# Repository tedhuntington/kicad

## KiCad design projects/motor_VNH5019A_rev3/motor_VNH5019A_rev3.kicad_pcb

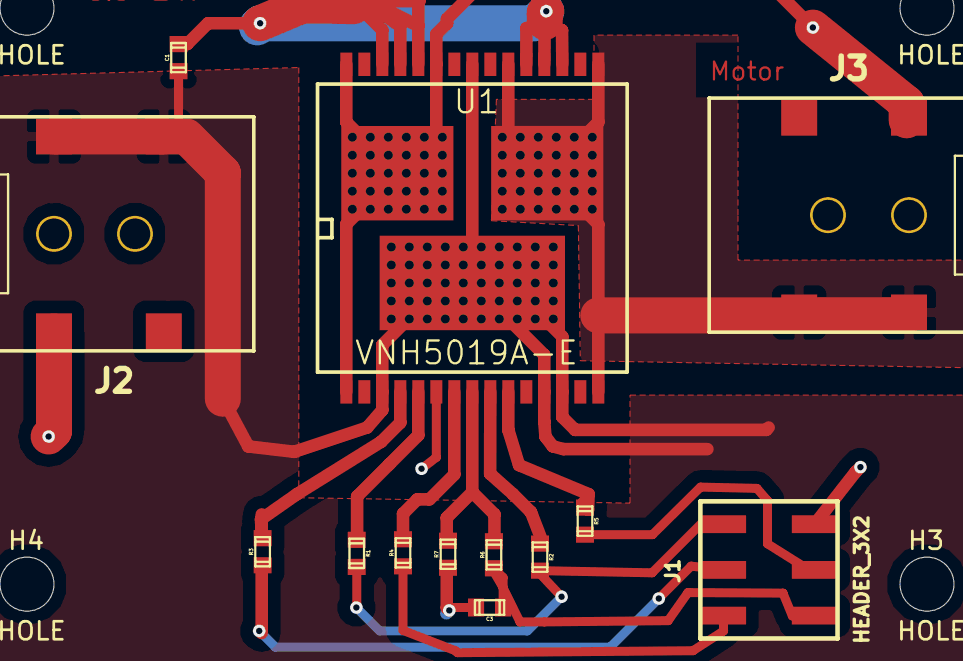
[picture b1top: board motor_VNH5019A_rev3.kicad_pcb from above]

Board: 2 copper layers, 17 parts (0 on the bottom side), 15 nets.

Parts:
C1: .1uF (50v); TED_SM0603
C3: 33nF; TED_SM0603
H1, H2, H3, H4: HOLE; TED_Hole_3mm
J1: HEADER_3X2; TED_HEADER_3x2_SMT
J2, J3: DC_2.1MM; TED_DC_2.1mm_SMT
R1, R2: 3.3k; TED_SM0603
R3, R4, R5: 1k; TED_SM0603
R6: 10k; TED_SM0603
R7: 1.5k; TED_SM0603
U1: VNH5019A-E; TED_MultiPowerSO-30

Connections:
+2.8v: J1.1, R1.2, R2.2
CS: R6.2, R7.2, U1.8
GND: C1.2, C3.2, J1.6, J2.2, R7.1, U1.6, U1.18, U1.19, U1.20, U1.26, U1.27, U1.28
IN_A: R3.2, U1.4
IN_B: R5.1, U1.10
Motor1OutA: J3.2, U1.1, U1.25, U1.30, U1.33
Motor1OutB: J3.1, U1.15, U1.16, U1.21, U1.32
unnamed: J1.3, R4.1
unnamed: R2.1, U1.9
unnamed: R1.1, U1.5
unnamed: J1.2, R3.1
unnamed: J1.5, R5.2
unnamed: C3.1, J1.4, R6.1
PWM: R4.2, U1.7
Vin: C1.1, J2.1, U1.3, U1.12, U1.13, U1.23, U1.31

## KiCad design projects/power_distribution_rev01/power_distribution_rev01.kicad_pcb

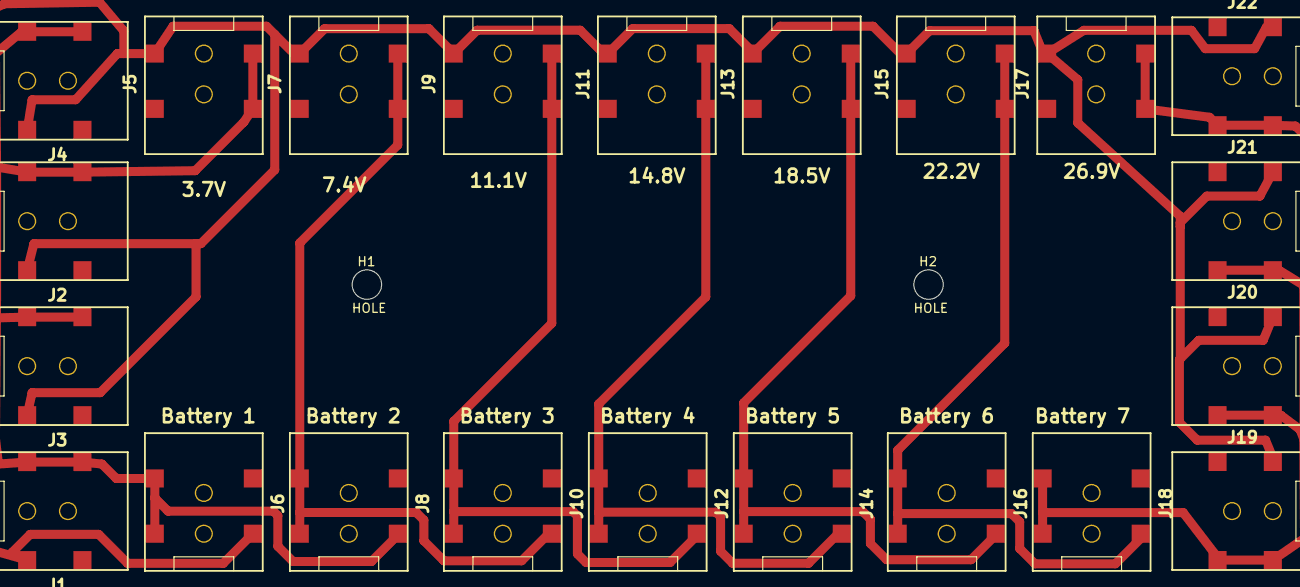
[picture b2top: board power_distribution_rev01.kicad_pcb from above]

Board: 2 copper layers, 24 parts (0 on the bottom side), 8 nets.

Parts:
H1, H2: HOLE; TED_Hole_3.25mm
J1, J2, J3, J4, J5, J6, J7, J8, J9, J10, J11, J12, J13, J14, J15, J16, J17, J18, J19, J20, J21, J22: DC_2.1MM; TED_DC_2.1mm_SMT

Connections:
GND: J1.2, J2.2, J3.2, J4.2, J5.2, J6.2, J7.2, J9.2, J11.2, J13.2, J15.2, J17.2, J19.2, J20.2, J21.2, J22.2
VBAT1: J1.1, J2.1, J3.1, J4.1, J5.1, J6.1, J8.2
VBAT2: J7.1, J8.1, J10.2
VBAT3: J9.1, J10.1, J12.2
VBAT4: J11.1, J12.1, J14.2
VBAT5: J13.1, J14.1, J16.2
VBAT6: J15.1, J16.1, J18.2
VBAT7: J17.1, J18.1, J19.1, J20.1, J21.1, J22.1

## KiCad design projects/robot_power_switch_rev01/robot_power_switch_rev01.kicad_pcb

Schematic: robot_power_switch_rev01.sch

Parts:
H1, H2: HOLE
J1, J2, J3, J4, J5, J6, J7, J8: DC_2.1MM; TED_DC_2.1mm
Q1: NMOSFET
Q2, Q3: PMOSFET
R1, R2: 1M

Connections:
GND: J1.2, J3.2, J8.2, Q1.2 (S), R1.2
unnamed: Q1.3 (D), Q3.1 (G), R2.2
PowerOutHigh: J2.2, J3.1
VBAT1: J4.1, Q2.2 (S)
VBAT2: J4.2, J5.1
VBAT3: J5.2, J6.1
VBAT4: J6.2, J7.1
VBAT5: J7.2, J8.1
VDD: J1.1, Q1.1 (G), Q2.1 (G), Q3.2 (S), R1.1, R2.1
VWallOrBattery: J2.1, Q2.3 (D), Q3.3 (D)

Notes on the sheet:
VDD=22v
AC ps is 22V 350W (15.9A)
Power Supply In
Power Switch
22V Power Out to Motherboard and Motors
Si7121ADN (-30Vds, +-25Vgs)
NMOS (Vds>=25v, Vgs+-30v)

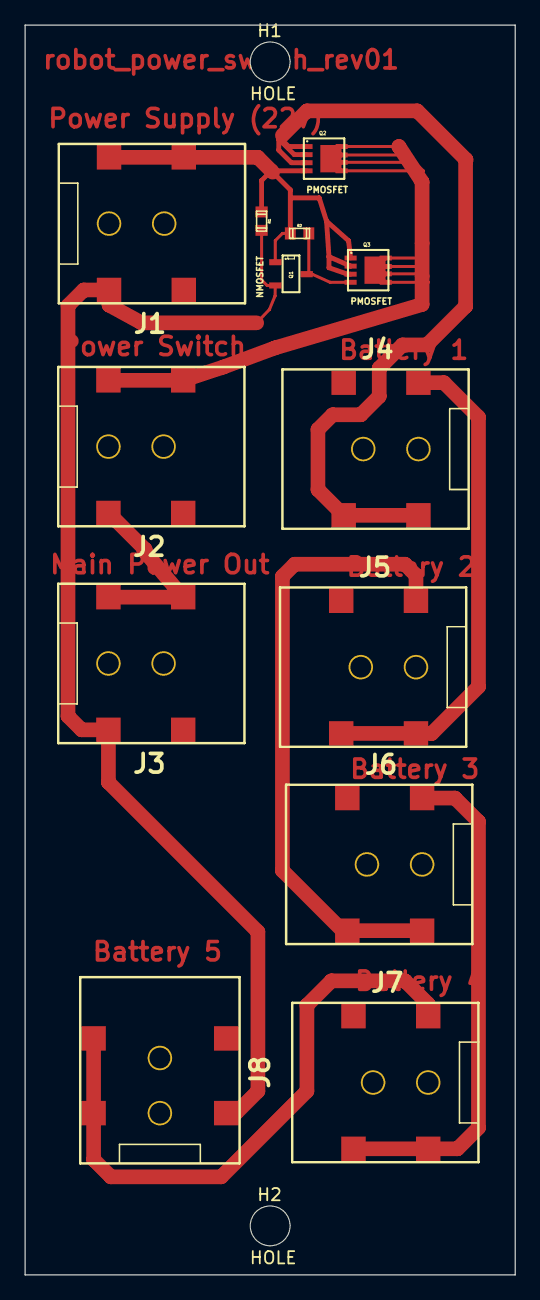
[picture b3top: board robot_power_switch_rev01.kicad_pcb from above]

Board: 2 copper layers, 40.0 x 102.0 mm, 15 parts (0 on the bottom side), 10 nets.

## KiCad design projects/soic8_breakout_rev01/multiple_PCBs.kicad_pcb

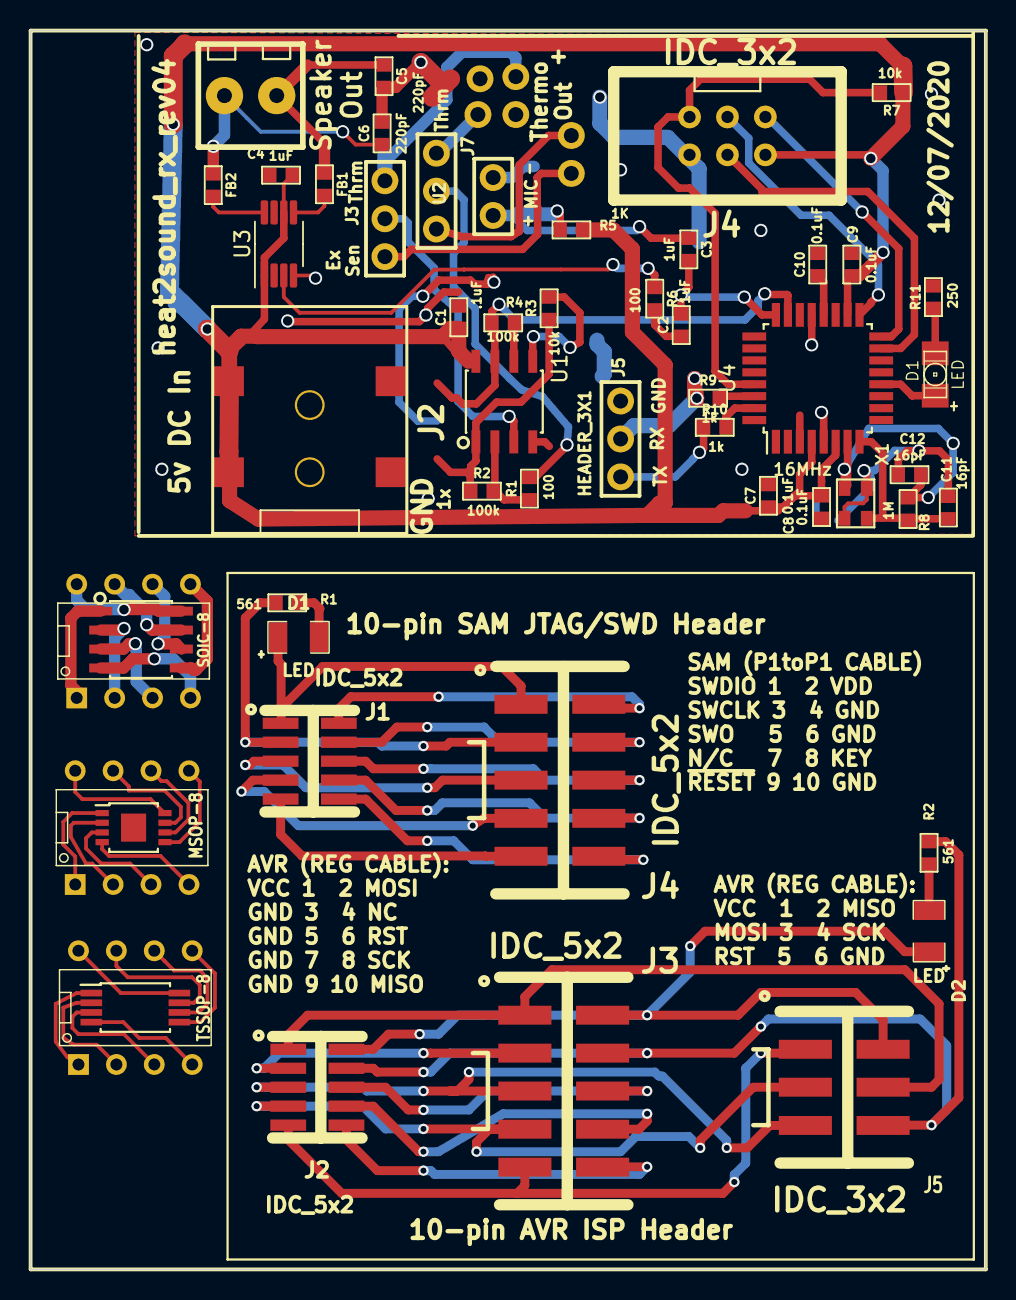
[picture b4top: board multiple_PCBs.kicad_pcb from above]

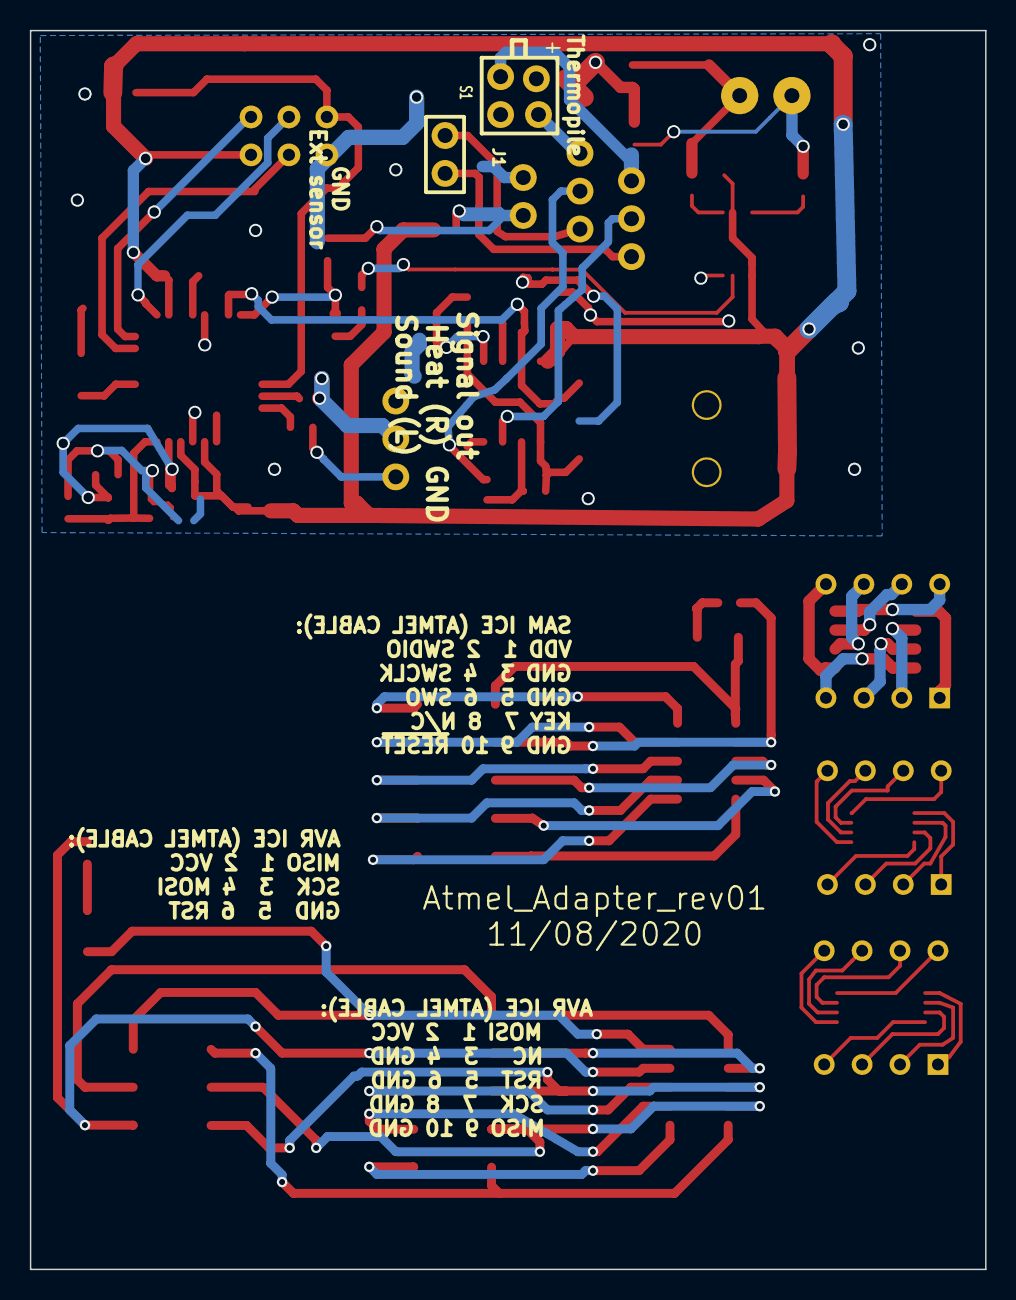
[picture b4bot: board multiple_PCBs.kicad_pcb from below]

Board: 2 copper layers, 64.0 x 83.0 mm, 54 parts (2 on the bottom side), 79 nets.

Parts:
C1: .1uF; TED_SM0603_C
C2, C3, C4: 1uF; TED_SM0603_C
C5, C6: 220pF; TED_SM0603_C
C7, C8, C9, C10: 0.1uF; TED_SM0603_C
C11, C12: 16pF; TED_SM0603_C
D1, D2: LED; TED_SM1206_LED
D1#2: LED; TED_LED-1206
FB1, FB2: ferrite_bead; TED_SM0603_R
J1, J2: IDC_5x2; TED_IDC_5x2_1.27pitch_SMD_nm
J1#2: TERMINAL_3.5MM_PCB_2PIN; TED_HEADER_2x1
J2#2: DC_2.1mm; TED_2.1mm_DC_SMD
J3, J4: IDC_5x2; TED_IDC_5x2_SMD
J3#2, J7: JUMPER_3X1; TED_HEADER_3x1
J4#2: IDC_3x2; TED_IDC_3x2
J5: IDC_3x2; TED_IDC_3x2_SMD
J5#2: HEADER_3X1; TED_HEADER_3x1
J6: TERMINAL_3.5MM_PCB_2PIN; TED_TERMINAL_3.5MM_2PIN
R1, R2: 561; TED_SM0603_R
R1#2, R6: 100; TED_SM0603_R
R2#2, R4: 100k; TED_SM0603_R
R3, R7: 10k; TED_SM0603_R
R5: 1K; TED_SM0603_R
R8: 1M; TED_SM0603_R
R9, R10: 1k; TED_SM0603_R
R11: 250; TED_SM0603_R
S1: THERMOPILE_MLX90247; TED_HEADER_2x2_THERMO
U1: Generic_8-pin_IC; SOIC-8
U1#2: MCP6V02; SOIC-8
U2, U5, U6: Generic_8-pin_Module; TED_DIP-8
U2#2: MIC; TED_HEADER_2x1
U3: Generic_8-pin_IC; TSSOP-8_4.4x3mm_P0.65mm
U3#2: PAM8302A; MSOP-8_3x3mm_P0.65mm
U4: Generic_8-pin_IC; MSOP-8-1EP_3x3mm_P0.65mm_EP1.68x1.88mm
U4#2: ATMEGA328P-AU; TQFP-32_7x7mm_Pitch0.8mm
X1: 16MHz; crystal_TSX3225

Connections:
+5v: C1.1, C4.1, C7.1, C8.1, C9.1, J2#2.1, J4#2.2, R5.1, R7.1, U1#2.8, U3#2.1, U3#2.6, U4#2.4, U4#2.6, U4#2.18
/a1: U1.1, U2.1
/a2: U1.2, U2.2
/a3: U1.3, U2.3
/a4: U1.4, U2.4
/a5: U1.5, U2.5
/a6: U1.6, U2.6
/a7: U1.7, U2.7
/a8: U1.8, U2.8
/b1: U4.1, U6.1
/b2: U4.2, U6.2
/b3: U4.3, U6.3
/b4: U4.4, U6.4
/b5: U4.5, U6.5
/b6: U4.6, U6.6
/b7: U4.7, U6.7
/b8: U4.8, U6.8
/c1: U3.1, U5.1
/c2: U3.2, U5.2
/c3: U3.3, U5.3
/c4: U3.4, U5.4
/c5: U3.5, U5.5
/c6: U3.6, U5.6
/c7: U3.7, U5.7
/c8: U3.8, U5.8
ADC0: R4.1, U1#2.7, U4#2.23
ADC1: C2.2, C3.2, U4#2.24
GND: C1.2, C4.2, C5.2, C6.2, C7.2, C8.2, C9.2, C10.2, C11.2, C12.2, J2#2.2, J4#2.6, J5#2.1, R11.2, U1#2.4, U2#2.2, U3#2.4, U4#2.3, U4#2.5, U4#2.21, X1.2, X1.4
MISO: J4#2.1, U4#2.16
MOSI: J4#2.4, U4#2.15
unnamed: C2.1, R6.2
unnamed: C3.1, R5.2, U2#2.1
unnamed: C5.1, FB1.1, J6.2
unnamed: C6.1, FB2.1, J6.1
unnamed: C10.1, U4#2.20
unnamed: C11.1, R8.2, U4#2.8, X1.3
unnamed: C12.1, R8.1, U4#2.7, X1.1
unnamed: D1#2.1, U4#2.12
unnamed: D1.2, D1#2.2, R1.1, R11.1
unnamed: D2.2, R2.1
unnamed: FB1.2, U3#2.5
unnamed: FB2.2, U3#2.8
unnamed: J1#2.1, J7.1
unnamed: J1#2.2, J3#2.1
unnamed: J3#2.2, U1#2.3
unnamed: J3#2.3, S1.1
unnamed: J5#2.2, R9.1
unnamed: J5#2.3, R10.1
unnamed: J7.2, R1#2.2
unnamed: J7.3, S1.3
unnamed: R1#2.1, R2#2.2, U1#2.2
unnamed: R2#2.1, R3.1, U1#2.1
unnamed: R3.2, U1#2.5
unnamed: R4.2, U1#2.6
unnamed: R6.1, U3#2.3
RX: R9.2, U4#2.30
SCLK: J4#2.3, U4#2.17
TX: R10.2, U4#2.31
apin1: J2.1, J3.1, J5.4
apin2: D2.1, J2.2, J3.2, J5.2
apin3: J2.3, J3.3
apin4: J2.4, J3.4, J5.6, R2.2
apin5: J2.5, J3.5, J5.5
apin6: J2.6, J3.6
apin7: J2.7, J3.7, J5.3
apin8: J2.8, J3.8
apin9: J2.9, J3.9, J5.1
apin10: J2.10, J3.10
pin1: D1.1, J1.1, J4.1
pin2: J1.2, J4.2
pin3: J1.3, J4.3, R1.2
pin4: J1.4, J4.4
pin5: J1.5, J4.5
pin6: J1.6, J4.6
pin7: J1.7, J4.7
pin8: J1.8, J4.8
pin9: J1.9, J4.9
pin10: J1.10, J4.10
~RESET: J4#2.5, R7.2, U4#2.29
